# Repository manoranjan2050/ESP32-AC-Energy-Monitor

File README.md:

# ESP32-S3 AC Energy Monitor (6 CT + voltage), ESPHome / Home Assistant

An open-source, DIY mains energy monitor built on an **ESP32-S3 DevKit**:
- up to **6 SCT-013 current transformers (CTs)**, each channel works with **100A/50mA** or **30A/1V** CTs
- one **ZMPT101B** voltage sensor
- **ESPHome** firmware, visible in **Home Assistant**

> **⚠ Not a certified energy meter.** The ESP32 ADC is noisy and non-linear. Don't use this for
> billing or protection. The board has a **230 V section**, so build and test it only if you're
> competent with mains wiring.

---

## Project status (2026-09-24)

| Part | Status |
|---|---|
| Stage-1 test firmware (1 CT, true RMS, calibration in HA) | ✅ Working (`esphome/energy_monitor_test.yaml`) |
| CT input circuit (bias + 1k/1.8k + 104 + burden) | ✅ **Proven on a breadboard** with both CT types (results below) |
| Custom PCB v0.1 (KiCad): 6 CT + on-board ZMPT101B | ✅ Designed and **fully routed**. ERC 0, DRC 0 errors, schematic ↔ PCB parity 0. **Not built yet** |
| On-board ZMPT101B + MCP6002 voltage stage | ⚠ Designed, **not tested yet** |
| 6-channel + voltage firmware (real power, PF, kWh) | ⏳ Next step (after the PCB) |

### Breadboard test results (CT channel = same values as the PCB)

| CT | Load | Reading | Notes |
|---|---|---|---|
| 30A/1V | CT unclamped | ~0.08 A | Noise floor |
| 30A/1V | Light + fan | **0.33 A** | ≈ 75 W |
| 30A/1V | Water heater | **12.66 A** | Clean sine (pp/rms 2.86), no clipping |
| 100A/50mA + 24 Ω burden | Induction cooker | **4.6 A** | Stable, no clipping |

---

## Repository map

```
esphome/
  energy_monitor_test.yaml      Stage-1 test firmware (1 CT on GPIO1)
  secrets.example.yaml          Copy to secrets.yaml (git-ignored) and fill in Wi-Fi/keys
docs/wiring.md                  Stage-1 breadboard wiring checks
hardware/
  README.md                     PCB design notes, calculations, before-ordering checklist
  kicad/                        KiCad 10 project (schematic + routed PCB + ZMPT101B footprint + DRC rules)
  fab/                          Manufacturing files: Gerbers zip, BOM, pick-and-place, KiCad zip
  renders/                      Diagrams (SVG), PCB images, schematic PDF
  generate_kicad.py             Builds schematic + PCB from ONE netlist (source of truth)
  route_pcb.py                  Hand-routes mains, autoroutes the rest with Freerouting
  make_*_svg.py                 Regenerate the SVG diagrams from the same netlist
```

---

## Files you'll use

### KiCad (schematic + PCB)

| File | What it is |
|---|---|
| [`hardware/kicad/ct6-energy-monitor.kicad_pro`](hardware/kicad/ct6-energy-monitor.kicad_pro) | **Open this in KiCad 10** (free, kicad.org). The schematic and PCB open together |
| [`hardware/kicad/ct6-energy-monitor.kicad_sch`](hardware/kicad/ct6-energy-monitor.kicad_sch) | Schematic: 81 parts, 42 nets |
| [`hardware/kicad/ct6-energy-monitor.kicad_pcb`](hardware/kicad/ct6-energy-monitor.kicad_pcb) | Routed 2-layer PCB, 120 × 90 mm |
| [`hardware/fab/ct6-kicad-project.zip`](hardware/fab/ct6-kicad-project.zip) | The whole KiCad project in one zip |
| [`hardware/renders/schematic.pdf`](hardware/renders/schematic.pdf) | Schematic as a PDF, for viewing and printing |

### EasyEDA

- **EasyEDA Pro:** *File → Import → KiCad*, then pick `ct6-energy-monitor.kicad_pro` or `ct6-kicad-project.zip`.
  The files are **KiCad 10 format**, and EasyEDA's importer may only accept older KiCad versions (**not tested**).
- **EasyEDA Standard:** only imports old KiCad 5 files, so it won't work.
- **If the import fails**, you have three options:
  1. **Order straight from the Gerbers** (below). The board is already routed, so no EasyEDA is needed.
  2. **Redraw in EasyEDA** using [`easyeda_connection_guide.svg`](hardware/renders/easyeda_connection_guide.svg).
     It shows every part, every pin and its net name. Place the parts, put a **Net Label** with the exact
     name on each pin, then check the nets against the list in section 7 of that SVG.
  3. Ask for a **KiCad 6-format copy** of the schematic, which EasyEDA Pro is more likely to accept.

### v0.2 for EasyEDA: ESP32-S3-WROOM-1U module on board (in progress)

[`hardware/renders/easyeda_v02_wroom1u_guide.svg`](hardware/renders/easyeda_v02_wroom1u_guide.svg) is the
EasyEDA build guide for **v0.2**: 97 parts and 51 nets, every pin with its net name. It's generated by
`hardware/make_easyeda_v02_svg.py`.

**Changes from v0.1:**
- The DevKit sockets are replaced by **ESP32-S3-WROOM-1U-N16R8** (LCSC C3013946). Its U.FL connector takes an external IPEX antenna, which works much better from inside a metal DB box.
- **New support parts:**
  - **AMS1117-3.3** regulator
  - **USB-C with data** (D+ → IO20, D− → IO19) and **USBLC6-2SC6** ESD protection
  - **RESET/BOOT** buttons and a UART header
- **ZMPT101B backup:** **J8** takes the plug-in module, and jumper **JP2** selects what feeds GPIO9 (1-2 = on-board stage, 2-3 = module).
- **Unchanged:** the CT channels, bias, on-board voltage stage and GPIO map.

**v0.2 KiCad schematic** (schematic only; you lay out the v0.2 PCB in EasyEDA):
- [`hardware/kicad_v02/ct6-energy-monitor-v02.kicad_pro`](hardware/kicad_v02/ct6-energy-monitor-v02.kicad_pro): open in KiCad 10
- [`hardware/renders/schematic_v02.pdf`](hardware/renders/schematic_v02.pdf): PDF view
- [`hardware/fab/ct6-v02-kicad-schematic.zip`](hardware/fab/ct6-v02-kicad-schematic.zip): zipped project; try *EasyEDA Pro → File → Import → KiCad*
- [`hardware/kicad_v02/ct6-v02-bom.csv`](hardware/kicad_v02/ct6-v02-bom.csv): BOM

**Checks passed:**
- KiCad ERC: **0 electrical errors**
- **All 242 pin connections / 51 nets match** `hardware/netlist_v02.py`, which also generates the EasyEDA guide, so both always agree
- The module pinout was checked against KiCad's official ESP32-S3-WROOM-1 symbol

Regenerate with `python hardware/generate_kicad_v02.py`.

### Ordering (JLCPCB)

| File | Use |
|---|---|
| [`hardware/fab/ct6-gerbers-jlcpcb.zip`](hardware/fab/ct6-gerbers-jlcpcb.zip) | Upload as-is: Gerbers + drill, 2 layers |
| [`hardware/fab/ct6-bom.csv`](hardware/fab/ct6-bom.csv) | Bill of materials |
| [`hardware/fab/ct6-cpl.csv`](hardware/fab/ct6-cpl.csv) | Pick-and-place, origin = bottom-left board corner |

### Diagrams (SVG, open in any browser)

| Diagram | Shows |
|---|---|
| [`pcb_full_connection.svg`](hardware/renders/pcb_full_connection.svg) | **The complete PCB circuit**: every R, C, diode, jumper, op-amp pin and GPIO |
| [`easyeda_connection_guide.svg`](hardware/renders/easyeda_connection_guide.svg) | Every part as a card: pin → net name. Use it for EasyEDA redraws and checks |
| [`final_6ct_voltage_connection.svg`](hardware/renders/final_6ct_voltage_connection.svg) | Breadboard version: 6 CT + ready-made ZMPT101B module |
| [`breadboard_connection.svg`](hardware/renders/breadboard_connection.svg) | Breadboard test of one CT channel (the proven circuit) |
| [`pcb_top.png`](hardware/renders/pcb_top.png), [`pcb_copper.png`](hardware/renders/pcb_copper.png) | PCB 3D render and copper view |

---

## How the circuit works

### GPIO map (ESP32-S3, ADC1 only)

| Signal | GPIO | DevKit socket pin |
|---|---|---|
| CT1 | GPIO1 | J4-4 |
| CT2 · CT3 · CT4 · CT5 | GPIO4 · 5 · 6 · 7 | J3-4 · 5 · 6 · 7 |
| CT6 | GPIO8 | J3-12 |
| Voltage (ZMPT101B) | GPIO9 | J3-15 |
| Bias monitor | GPIO10 | J3-16 |
| I²C OLED SDA / SCL | GPIO17 / GPIO18 | J3-10 / J3-11 |
| 5V in / 3V3 / GND | — | J3-21 / J3-1,2 / J3-22, J4-1,21,22 |

Avoid GPIO0/3/45/46 (strapping), GPIO35–37 (octal PSRAM on N16R8) and GPIO11–20 (ADC2, conflicts with Wi-Fi).
**Measure your DevKit before ordering.** On the test board the silkscreen "4" was really GPIO1.

### One CT channel (×6, identical)

```
CT sleeve ─────────────────────────────────────── VB (bias ≈ 1.5 V)
CT tip ──┬── 1 kΩ ──┬── ADC node ──► GPIO
         │          ├── 1.8 kΩ ──► VB
       22 Ω         ├── 100 nF (104) ──► GND
     (burden,       └── BAT54S clamp (to GND and +3V3A)
   via jumper JP)
```

- **1 kΩ + 1.8 kΩ** scale the signal to **×0.643** around the bias. This gives headroom for 100 A, and the 1 kΩ limits current into the pin.
- **100 nF** filters noise (~2.5 kHz).
- **BAT54S** clamps the pin between 0 and 3.3 V. See "Diodes" below.

### Jumpers JP11…JP16 (one per CT)

| CT type | Shunt position | Burden | Home Assistant settings |
|---|---|---|---|
| **100A/50mA** (SCT-013-000) | **1-2 (mA), default** | IN | Burden **22** (or 24) · Secondary **0.05** · Primary **100** · Calibration **1.555** |
| **30A/1V** (SCT-013-030) | **2-3 (V)** | OUT | Burden **1** · Secondary **1** · Primary **30** · Calibration **1.555** |

- **1.555** undoes the ×0.643 divider. Fine-tune each channel: `Cal = 1.555 × (clamp-meter A ÷ reading A)`.
- **A 1V CT with the shunt on mA** reads ~25 % of the true value. That's safe, just obviously wrong.
- **⚠ A 100A CT with the shunt on V runs OPEN.** The reading clips to 0/4095 and can damage the CT or the pin. **Unclamp immediately.**
- Ship boards with every shunt on **1-2**.

### Diodes (D…)

| Designator | Part | Job |
|---|---|---|
| **D1** | SS34 Schottky | Power input: reverse-polarity protection, and stops USB 5V back-feeding your 5V supply |
| **D11 … D16** | BAT54S | ADC clamps for **CT1 … CT6** (D1**n** = CT**n**, so **D16 = CT6 → GPIO8**) |
| **D41** | BAT54S | ADC clamp for the voltage channel (GPIO9) |

A **BAT54S** is two Schottky diodes in series in one SOT-23:
- **pin 1 = GND side**
- **pin 2 = +3V3A side**
- **pin 3 = ADC node**

It does nothing while the signal is between 0 and 3.3 V. If a fault pushes the pin outside that range (for example a CT without its burden), it clamps the pin. The 1 kΩ in front limits the current. The clamps were optional on the breadboard; **fit them on the PCB.**

### Parts naming (per CT channel n = 1…6)

`J1n` jack · `R1n1` 22 Ω burden · `JP1n` mA/V jumper · `R1n2` 1 kΩ · `R1n3` 1.8 kΩ · `C1n` 100 nF · `D1n` BAT54S

### Resistor colour codes (4-band)

| Value | Bands |
|---|---|
| 10 kΩ | brown · black · orange |
| 1 kΩ | brown · black · red |
| 1.8 kΩ | brown · grey · red |
| 22 Ω | red · red · black |
| 24 Ω | red · yellow · black |
| 18 Ω | brown · grey · black (⚠ not 18 kΩ = brown · grey · orange) |

A ceramic cap marked **104** = 100 nF; **103** = 10 nF; **473** = 47 nF.

---

## Working on another PC

```bash
git clone https://github.com/manoranjan2050/ESP32-AC-Energy-Monitor.git
```

- **PCB:** install KiCad 10 and open `hardware/kicad/ct6-energy-monitor.kicad_pro`.
- **Firmware:** copy `esphome/secrets.example.yaml` to `esphome/secrets.yaml` (git-ignored) and fill in your Wi-Fi and keys.
- **Regenerate** (optional; this overwrites the KiCad files, so **don't** run it after editing the board by hand):

  ```bash
  "C:/Program Files/KiCad/10.0/bin/python.exe" hardware/generate_kicad.py
  ```

## Before ordering the PCB

1. Measure the **DevKit header row spacing** (22.86 mm) and check every pin used.
2. Check the **ZMPT101B pin grid**: 10.0 × 12.7 mm, with calipers.
3. **Screw terminals:** the wire entry faces the board edge.
4. Keep the **6.5 mm mains creepage** and the **slot under T1**.
5. **First power-up without mains and without CTs.** Expect +3V3A ≈ 3.3 V, VB ≈ 1.50 V, and every CTn_ADC / V_ADC ≈ 1.50 V.

Full details are in [`hardware/README.md`](hardware/README.md).

---

## Next steps

1. Order and build PCB v0.1, then test it: the CT channels first, then the on-board voltage stage (untested so far).
2. **6-channel + voltage ESPHome firmware:**
   - per-channel CT type, ratio and calibration
   - V + I sampled together for **real power, power factor, frequency and kWh**
   - Home Assistant **Energy dashboard** support

---

# Stage-1 test firmware guide (1 CT, breadboard)

> The sections below document the **first single-CT test**. Its bias circuit (10k/10k) and direct CT
> wiring were the starting point. The **final, proven channel circuit** adds the 1 kΩ / 1.8 kΩ / 104
> network shown above: use [`breadboard_connection.svg`](hardware/renders/breadboard_connection.svg) and set
> **Calibration 1.555**.

- Board: **ESP32-S3** (QFN56 rev v0.2, 16 MB flash, 8 MB PSRAM, native USB)
- ESPHome: **2026.8.2**, esp-idf framework
- Firmware: [`esphome/energy_monitor_test.yaml`](esphome/energy_monitor_test.yaml)
- Wiring checks: [`docs/wiring.md`](docs/wiring.md)

## 1. Hardware wiring (overview)

```
                     ESP32-S3 3V3
                          │
                         10k
                          │
             ┌────────────┼──────────── BIAS node (~1.65 V)
             │            │                 │
             │           10k            [10 µF, optional
             │            │              but recommended]
             │           GND                │
             │                             GND
   SCT-013-000
   ┌───────────┐
   │ lead A ───┼──────────┬──────── BIAS node
   │           │         22 Ω   (burden, directly across the CT leads)
   │ lead B ───┼──────────┴──────── ESP32-S3 GPIO1 (ADC1_CH0)
   └───────────┘
```

The CT drives an AC voltage across the 22 Ω burden. Because one end of the
burden sits on the 1.65 V bias node, the ADC pin sees **1.65 V ± the AC signal**.

## 2. ESP32 ADC pin configuration

Set the pin in the `substitutions:` block. Give the GPIO **number only**:

```yaml
ct_gpio: "1"     # GPIO1 = ADC1 channel 0 (check the pin electrically; header labels can be misleading)
```

On the ESP32-S3 use an **ADC1 pin, GPIO1 to GPIO10**. Skip GPIO3 (it's a strapping pin).
Don't use ADC2 (GPIO11 to GPIO20), because Wi-Fi uses ADC2.

- Attenuation is **12 dB**. On the S3 that gives about 0 to 3.1 V of usable range.
- Every sample is converted with ESP-IDF's **eFuse curve-fitting calibration**,
  so the ADC is not treated as linear. The diagnostic entity
  **CT ADC Calibration** shows which scheme is active. If it says
  `UNCALIBRATED`, the linear 3.3 V/4095 fallback is in use and the voltages are rough.

## 3. The 22 Ω burden resistor

The SCT-013-000 is a **current-output CT** (100 A : 50 mA) and has **no internal burden**.
The 22 Ω resistor turns its current into a voltage:

| Primary current | Secondary current | Burden RMS | Burden peak | ADC swing (around 1.65 V) |
|---|---|---|---|---|
| 1 A     | 0.5 mA  | 11 mV   | 15.6 mV | ±0.016 V |
| 4.35 A (1 kW) | 2.17 mA | 47.9 mV | 67.7 mV | ±0.068 V |
| 10 A    | 5 mA    | 110 mV  | 156 mV  | ±0.156 V |
| 50 A    | 25 mA   | 550 mV  | 778 mV  | ±0.78 V |
| ~90 A   | 45 mA   | 990 mV  | 1.40 V  | about the S3 ADC limit |
| 100 A   | 50 mA   | 1.10 V  | 1.556 V | **clips** (0.09 to 3.21 V) |

With 22 Ω the usable range is about 0 to 90 A. The **CT Clipped Samples** entity counts samples at the ADC rails.

## 4. The 2 × 10 k bias circuit

The two 10 k resistors from 3V3 to GND make a mid-rail point (~1.65 V), so the AC
signal swings around it instead of going below 0 V. Put a
**10 µF to 100 µF capacitor from the bias node to GND**. Without it the bias node
picks up ripple and noise, which shows up as a higher no-load RMS. The firmware
measures the real bias every window (**CT Bias Voltage**), so it doesn't need to be exactly 1.65 V.

## 5. SCT-013-000 connection

The 3.5 mm jack uses **tip** and **sleeve** for the two secondary leads. The ring is
normally unused. Polarity doesn't matter for RMS. Use a 3.5 mm breakout, or cut
the plug and solder the leads. **Fit the burden before clamping the CT on anything.**

## 6. Flashing the ESP32-S3

**Option A: ESPHome Builder (Home Assistant add-on)**
1. ESPHome Builder → **Secrets** (top-right). Add the lines from
   `esphome/secrets.yaml` (not in git; copy `esphome/secrets.example.yaml` and fill in your values) (`wifi_ssid`, `wifi_password`, `ct_test_api_key`,
   `ct_test_ota_password`, `ct_test_ap_password`).
2. **+ New device** → *Continue* → *Skip* the wizard, or create any device and then
   **Edit** it. Replace the whole YAML with `energy_monitor_test.yaml` and save.
3. **Install** → *Plug into this computer* (Chrome/Edge Web Serial), or
   *Manual download* → *Factory format* and flash with web.esphome.io.
4. Later updates can go over the air: **Install → Wirelessly**.

**Option B: ESPHome CLI on this PC**
```bash
cd "D:/My Project/ElectroIoT/ESP32-AC-Energy-Monitor/esphome"
```
```bash
python -m esphome run energy_monitor_test.yaml --device COM5
```
If the S3 won't enter download mode, hold **BOOT**, tap **RST**, then release BOOT.

## 7. Adding it to Home Assistant

The device uses the ESPHome native API, so HA should discover it automatically
(**Settings → Devices & services → Discovered: CT Energy Test → Configure**). When
asked for the encryption key, enter the `ct_test_api_key` value. If it isn't
discovered, add the **ESPHome** integration manually with host `ct-energy-test.local`
(or its IP address) and port `6053`.

Entities (all published together every **5 s**, one window each):

| Entity | Meaning |
|---|---|
| CT Raw ADC | Last raw 12-bit sample in the window |
| CT ADC Voltage | Last sample converted to volts (calibrated) |
| CT Bias Voltage | Mean of the window, which is the DC bias the RMS is taken around |
| CT Minimum / CT Maximum | Lowest and highest raw counts in the window |
| CT Peak-to-Peak | Calibrated V(max) − V(min) |
| CT AC RMS | **True RMS of the AC part across the burden** (bias removed; 400 samples over 10 cycles) |
| CT Secondary / Primary Current (estimated) | Only while **CT Current Estimate Enabled** is on |
| CT Burden Resistance, CT Rated Primary/Secondary Current, CT Calibration Factor | Editable config numbers, kept across reboots |
| CT Clipped Samples, CT Actual Sample Rate, CT ADC Calibration | Diagnostics |

The current estimate is:
```
secondary_A = CT_AC_RMS / burden_resistance
primary_A   = secondary_A × (ct_primary_current / ct_secondary_current) × calibration_factor
```

## 8. Expected values with NO load (CT unclamped or on a dead cable)

| Entity | Expected |
|---|---|
| CT Bias Voltage | ~1.60 to 1.70 V (depends on the 3V3 rail and resistor tolerance) |
| CT Raw ADC / Min / Max | Around the bias count, roughly 1900 to 2300, with Min and Max only a few dozen counts apart |
| CT Peak-to-Peak | Small, about 10 to 60 mV (ADC noise) |
| CT AC RMS | **Low, about 1 to 10 mV** (noise floor) |
| CT Clipped Samples | 0 |
| CT Actual Sample Rate | ~2000 Hz |

Note your no-load RMS. It is the noise floor. As a rough guide, 5 mV of noise
equals about 0.45 A of "phantom" primary current.

## 9. What changes when you clamp a live conductor

Clamp **one** insulated conductor (live **or** neutral), not the whole cable. If
you clamp live and neutral together, their currents cancel and you read about 0.

With a **1000 W resistive load** (~4.35 A at 230 V):

| Entity | Load off | Load on (theory) |
|---|---|---|
| CT Bias Voltage | ~1.65 V | **Unchanged** (~1.65 V) |
| CT Min / Max | ±a few counts | Spread out by roughly ±85 counts |
| CT Peak-to-Peak | ~0.03 V | **~0.14 V** |
| CT AC RMS | ~0.005 V | **~0.048 V** |
| Primary Current (est., if enabled) | ~0.2 to 0.5 A (noise) | **~4.3 A** |

The HA history graph for **CT AC RMS** should step up when the load turns on and
drop when it turns off. To calibrate, compare against a trusted clamp meter and set
`CT Calibration Factor = meter_amps / estimated_amps`. Tip: pass the conductor
through the CT **5 times** (5 turns), so 4.35 A reads like 21.7 A. That gives a much
better signal-to-noise ratio for calibration (divide by 5 afterwards).

## 10. Safety warnings

- **Mains voltage (230 V AC) can kill.** Only clamp an insulated conductor.
  Never open or modify live wiring on a breadboard setup. If you're unsure, have a
  licensed electrician install the CT.
- **Never leave the SCT-013-000 secondary open-circuit while it's clamped on a
  loaded conductor.** A current-output CT with no burden can produce dangerously
  high voltages and damage itself. Keep the 22 Ω burden fitted whenever the CT is
  plugged in or clamped.
- **Never connect the CT directly to the ESP32 without the burden and bias.** The
  ADC pin must stay between 0 V and 3.3 V. A loose bias wire leaves the pin
  swinging below 0 V, which can damage the GPIO.
- The burden must match the current range. 22 Ω clips above ~90 A. For higher
  currents use a smaller burden (for example 18 Ω).
- The ESP32 is powered from USB and is **not isolated from anything except through
  the CT's own insulation**. Keep the breadboard away from the mains side.
- This firmware is not a certified meter. Don't use it for billing, protection, or
  safety decisions.

---

## Original roadmap (written before the 1-channel test)

The 1-channel test has since passed, and the 6-CT PCB is designed. See **Project status** and **Next steps** at the top of this README.

```
ESP32-S3
├── CT1 … CT8   (ADC1 GPIO1..10; per-channel burden + calibration)
└── ZMPT101B    (voltage)
```
Planned: RMS voltage, RMS current per CT, real/apparent power, power factor,
frequency, kWh with the HA Energy dashboard, per-channel calibration, MQTT option, and OTA.
Eight CTs plus a ZMPT101B is 9 analog inputs, which fits in ADC1's 10 pins on the S3. Real power needs
V and I sampled nearly at the same time, so the stage-2 design will use interleaved sampling (or an external
ADC such as the ADS1115/ADS131M08).

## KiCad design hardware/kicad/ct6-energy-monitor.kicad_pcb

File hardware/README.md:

# CT6 Energy Monitor PCB (v0.1): ESP32-S3 DevKit + 6 CT + ZMPT101B

KiCad 10 project: [`kicad/ct6-energy-monitor.kicad_pro`](kicad/ct6-energy-monitor.kicad_pro)
**Full circuit diagram (every R/C/jumper/GPIO): [`renders/pcb_full_connection.svg`](renders/pcb_full_connection.svg)** · Schematic PDF: [`renders/schematic.pdf`](renders/schematic.pdf) · 3D top view: [`renders/pcb_top.png`](renders/pcb_top.png) · BOM: [`bom.csv`](bom.csv)

> **Status: v0.1 fully routed. Not yet built or tested; do the breadboard test and the checklist below first.**
> ERC: 0 violations · DRC: 0 errors, **0 unconnected**, 0 creepage/clearance · schematic-to-PCB parity: 0 issues.
> Remaining DRC warnings are cosmetic only (silkscreen text overlaps, and the jack's edge marker moved off Edge.Cuts).

**Manufacturing files** (`fab/`):
- `ct6-gerbers-jlcpcb.zip`: Gerbers + drill, upload to JLCPCB as-is
- `ct6-bom.csv` and `ct6-cpl.csv`: BOM and pick-and-place (origin = bottom-left board corner)
- `ct6-kicad-project.zip`: the whole KiCad project

**EasyEDA:** EasyEDA Pro → *File → Import → KiCad*, then select `ct6-kicad-project.zip` (or the `.kicad_pro`).
The files are KiCad 10 format; if your EasyEDA version refuses them, order from the Gerber zip instead.
EasyEDA Standard only imports old KiCad 5 files.

Everything is generated from one netlist in [`generate_kicad.py`](generate_kicad.py), and routed by [`route_pcb.py`](route_pcb.py):
1. The 230 V nets are hand-routed as locked 0.8 mm tracks.
2. **Freerouting 1.9.0** autoroutes the rest, with the whole mains block (+6.5 mm) set as a keepout.
3. The GND pour is added last.

```bash
set CT6_NO_ZONES=1
"C:/Program Files/KiCad/10.0/bin/python.exe" hardware/generate_kicad.py
"C:/Program Files/KiCad/10.0/bin/python.exe" hardware/route_pcb.py path/to/freerouting-1.9.0.jar
```

⚠ Both scripts overwrite the `.kicad_pcb`. **If you edit the board by hand in KiCad, stop rerunning them.**

---

## Block diagram

```
 5V terminal / USB-C ─ polyfuse ─ SS34 ─► DevKit 5V ──► DevKit 3V3 ─ ferrite ─► +3V3A (analog)
                                                                               │
 +3V3A ─ 12k/10k ─► MCP6002-A buffer ─ 47R ─► VB = 1.50 V (10µF+100nF) ────────┼──► GPIO10 (bias monitor)
                                                                               │
 CT1..CT6 jack ─► [22R burden via mA/V jumper] ─ 1k ─┬─ 1k8 → VB              │
                                                      ├─ 100nF → GND           │
                                                      └─ BAT54S clamp ─► GPIO1,4,5,6,7,8
                                                                               │
 230V L/N ─ fuse 100mA ─ MOV ─ 4×220k ─► ZMPT101B ─► MCP6002-B TIA (2k7‖47nF) ─ 1k ─ BAT54S ─► GPIO9
```

## CT input channel (copied from KinCony KC868-M16v2, per channel)

| Part | Value | Purpose |
|---|---|---|
| J1n | 3.5 mm jack (SJ1-3523N) | **Tip = signal, Sleeve = VB**, Ring unused (SCT-013 wiring) |
| R1n1 | **22 Ω 0.1 %** | Burden for **mA-type** CTs (SCT-013-000 100 A/50 mA) |
| JP1n | 3-pin header | **1-2 = mA** (burden in, **ship with this fitted**); **2-3 = V** (burden out, for 1 V CTs such as SCT-013-030) |
| R1n2 / R1n3 | 1 kΩ / 1.8 kΩ 1 % | Attenuator: ×0.643 around VB. The 1 k limits current into the pin; the 1k8 holds an empty jack at VB |
| C1n | 100 nF | Anti-alias / noise filter, ~2.5 kHz |
| D1n | BAT54S | Clamps the ADC pin between GND and 3V3A |

**Headroom at the ADC pin** (1.50 V bias; S3 12 dB range is about 0 to 3.1 V):

| CT | At full scale | At the pin |
|---|---|---|
| SCT-013-000 + 22 Ω (jumper **mA**) | 100 A → 1.10 V RMS | ±1.00 V peak → 0.50 to 2.50 V ✅ |
| SCT-013-030 1 V (jumper **V**) | 30 A → 1.00 V RMS | ±0.91 V peak → 0.59 to 2.41 V ✅ |

Firmware scale (amps per RMS volt **measured at the pin**) = CT ratio ÷ 0.643:
- 100 A/50 mA + 22 Ω: 100 / 0.05 / 22 / 0.643 = **141.4 A/V**
- 30 A/1 V: 30 / 0.643 = **46.7 A/V**

Then fine-tune each channel's calibration factor against a clamp meter.

A **wrong jumper in one direction is safe**: a 1 V CT with the jumper on mA reads only **~25 % of the true value**, because its internal ~67 Ω burden ends up in parallel with the 22 Ω. It's obviously wrong, but harmless. **The dangerous case is an mA CT with the jumper on V.** In that state the CT runs open (the 0/4095 clipping from the breadboard test). That is why mA is the default and the 1k series resistor plus BAT54S protect the pin.

## Voltage channel (ZMPT101B, on board)

- **Primary:** 230 V → F2 100 mA T → 4 × 220 kΩ 1206 (880 kΩ, 57 V per resistor) → 0.26 mA. RV1 (275 VAC MOV) across L/N after the fuse.
- **Secondary:** into MCP6002-B used as a **transimpedance amplifier** with its + input at VB. Output = VB − 0.26 mA × 2.7 kΩ = **1.50 V ± 0.70 V RMS** (±1.0 V peak at 230 V, ±1.2 V at 270 V). 47 nF in parallel sets a ~1.25 kHz roll-off.
- Output goes through 1 kΩ + 100 nF + BAT54S to GPIO9. Calibrate volts in firmware; there's no trimmer.

## GPIO map (ESP32-S3, all ADC1)

| Signal | GPIO | DevKitC-1 pin |
|---|---|---|
| CT1 | GPIO1 | J3-4 (right header) |
| CT2 to CT6 | GPIO4, 5, 6, 7, 8 | J1-4..7, J1-12 (left header) |
| Voltage | GPIO9 | J1-15 |
| Bias monitor | GPIO10 | J1-16 |
| I2C OLED SDA / SCL | GPIO17 / GPIO18 | J1-10 / J1-11 |

Not used: GPIO0/3/45/46 (strapping), GPIO35 to 37 (octal PSRAM on N16R8), GPIO11 to 20 (ADC2, conflicts with Wi-Fi).

## PCB (120 × 90 mm, 2-layer)

- **Mains block** (top-left) is fenced by an **L-shaped 1.6 mm routed slot**. The slot's vertical leg runs **under the ZMPT101B** between primary and secondary pins (10 mm pin-to-pin).
- **Custom DRC rules** (`kicad/ct6-energy-monitor.kicad_dru`): **6.5 mm clearance and creepage** from any `AC_*` net to all low-voltage copper.
- **GND pour** on both layers covers the LV area only. It excludes the mains block and the **DevKit antenna area** (top-right; the DevKit's antenna end sits at the top board edge).
- CT jacks sit on the bottom edge. The DevKit's USB end points down into a clear area, so you can still plug in a USB cable for flashing.

## Before ordering (checklist)

1. **Measure your DevKit.** Header row spacing is set to **22.86 mm** (`DEVKIT_ROW_SPACING`), and the pin order is ESP32-S3-DevKitC-1. Your breadboard test showed the silkscreen didn't match the actual pin (the wire on "4" was GPIO1). **Check every pin used here with a meter or the pin-scan firmware.**
2. **ZMPT101B footprint:** 10.0 × 12.7 mm pin grid, cross-checked against two independent KiCad libraries. Check it against your part with calipers.
3. **Screw terminals J1/J5:** make sure the wire entry faces the board edge (rotate 180° in KiCad if not).
4. **Review the autorouted tracks** in KiCad. Autorouters are functional, not beautiful. The CT signal traces to the DevKit are long diagonals, which is fine at 50 Hz, but you may want to tidy them.
5. After any change, run DRC. It must show **0 unconnected items and 0 creepage errors**.
6. Mains safety: 230 V on a PCB needs an enclosure, a fuse, and no exposed metal. The ZMPT101B is the isolation barrier, so don't bypass it.

## Firmware

Not written yet. Extending `esphome/energy_monitor_test.yaml` to 6 CT + V gives:
- per-channel `ct_gpio`, CT type (mA/V), ratio and calibration
- interleaved V + I sampling for real power, PF and kWh

The on-board **attenuator (×0.643) must be included** in the scale; see the formulas above.

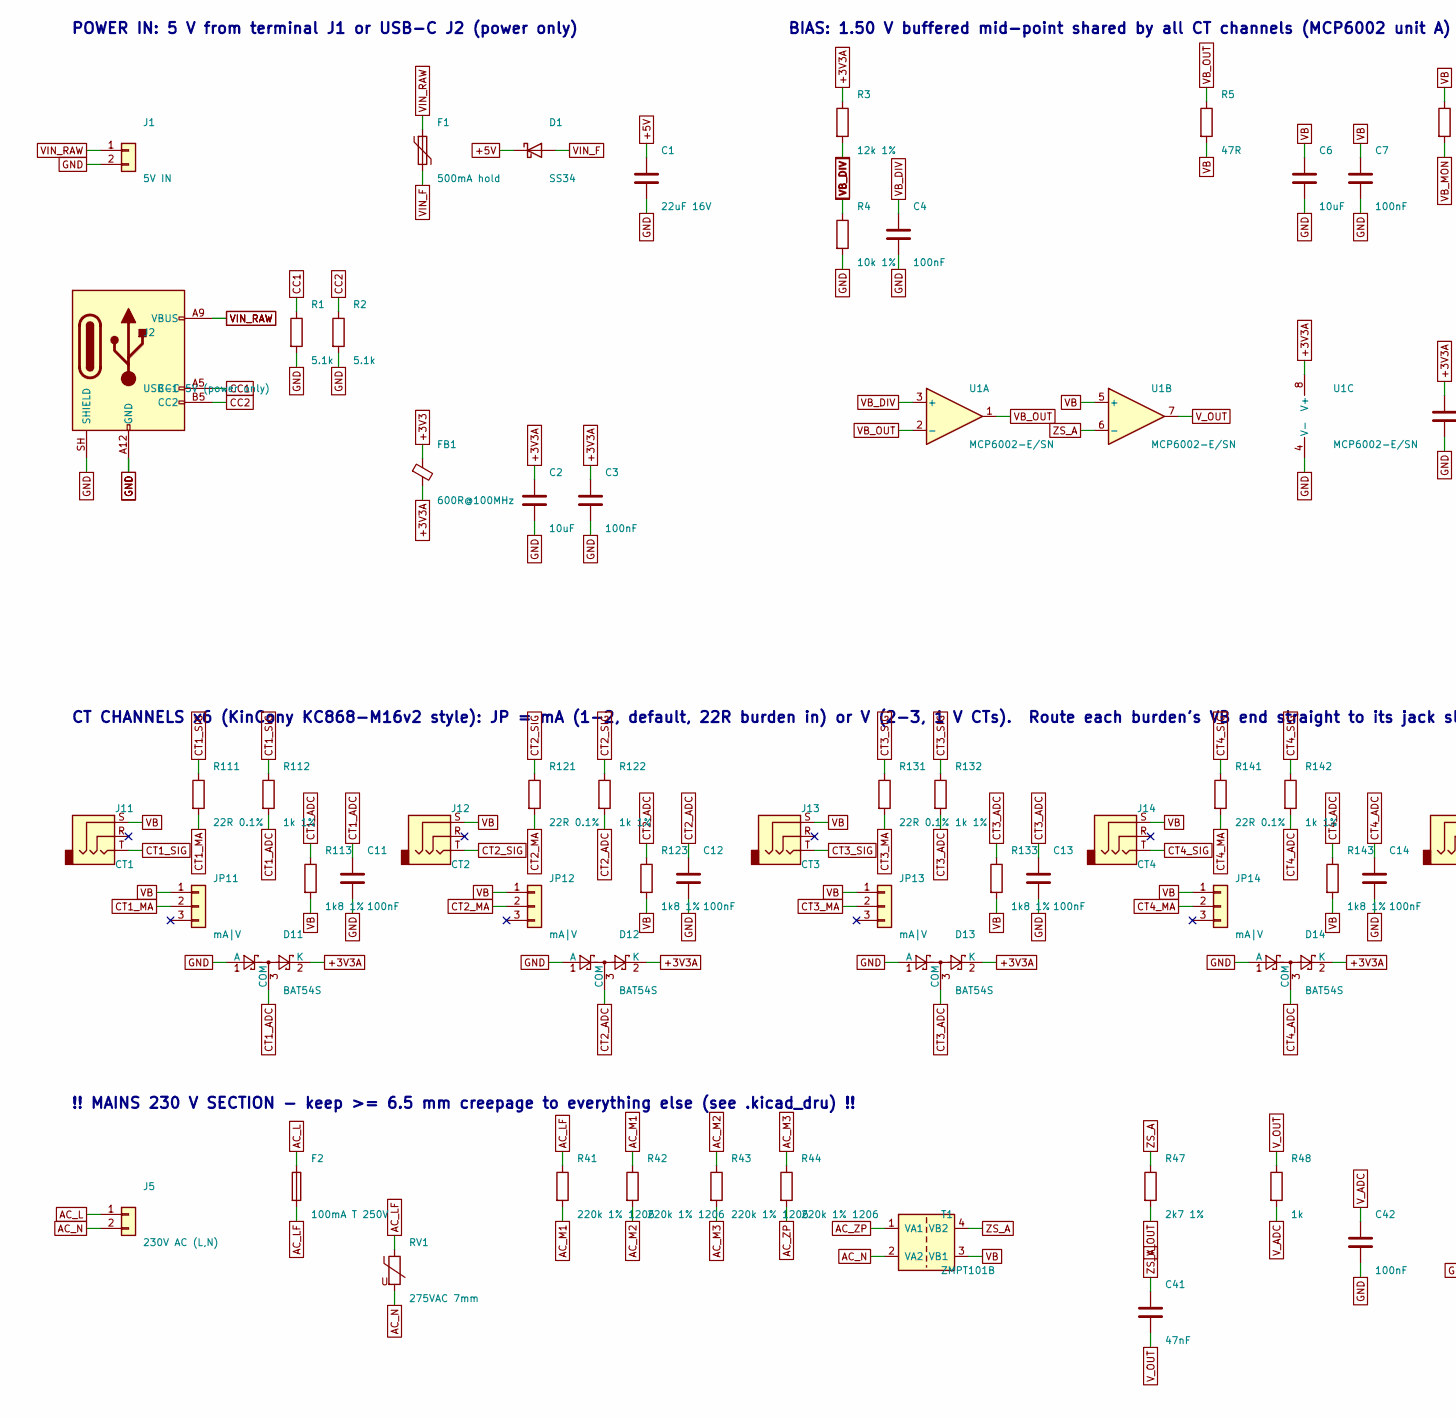
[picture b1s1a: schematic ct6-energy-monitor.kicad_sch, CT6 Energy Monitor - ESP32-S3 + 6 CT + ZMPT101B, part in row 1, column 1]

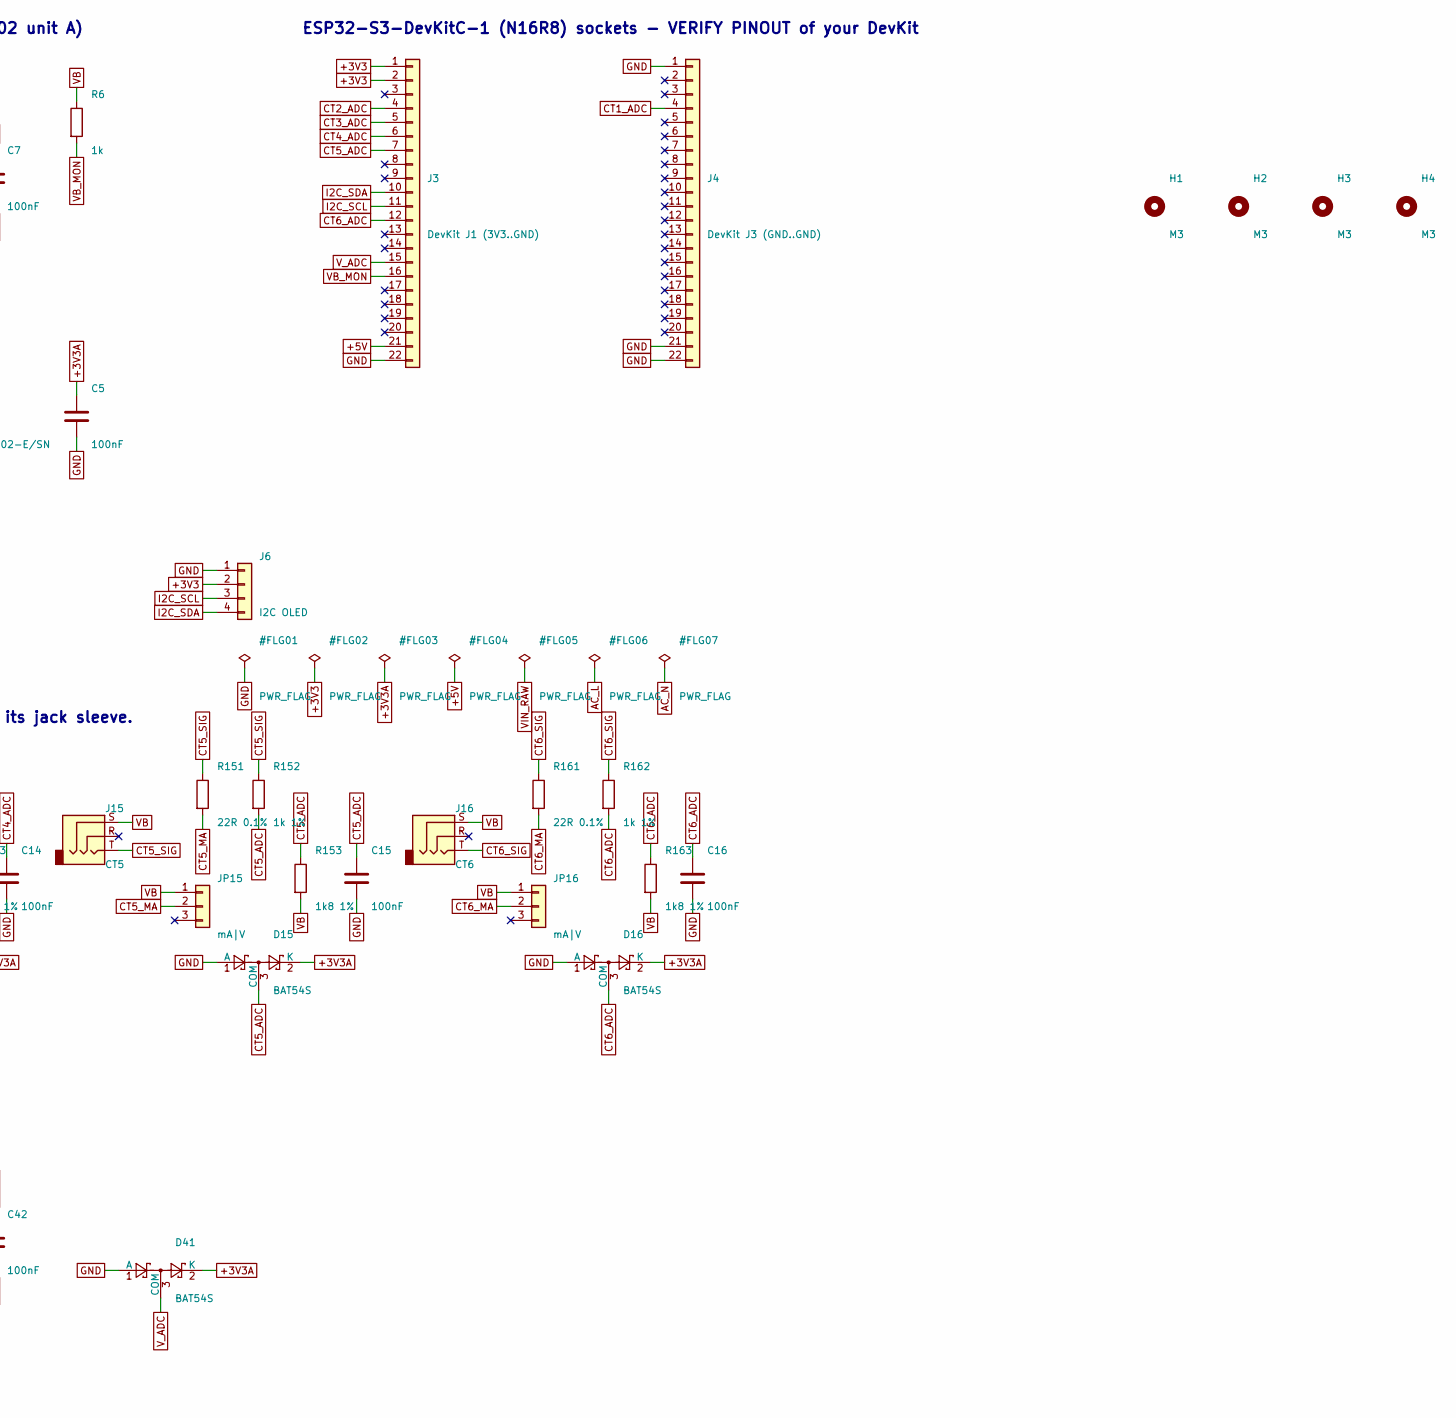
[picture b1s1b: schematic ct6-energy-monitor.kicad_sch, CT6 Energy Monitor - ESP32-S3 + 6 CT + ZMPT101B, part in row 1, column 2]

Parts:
C1: 22uF 16V; C_1206_3216Metric
C2, C6: 10uF; C_0805_2012Metric
C3, C4, C5, C7, C11, C12, C13, C14, C15, C16, C42: 100nF; C_0805_2012Metric
C41: 47nF; C_0805_2012Metric
D1: SS34; D_SMA
D11, D12, D13, D14, D15, D16, D41: BAT54S; SOT-23
F1: 500mA hold; Fuse_1206_3216Metric
F2: 100mA T 250V; Fuse_Littelfuse_395Series
FB1: 600R@100MHz; L_0805_2012Metric
H1, H2, H3, H4: M3; MountingHole_3.2mm_M3
J1: 5V IN; TerminalBlock_Phoenix_MKDS-1,5-2-5.08_1x02_P5.08mm_Horizont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
J2: USB-C 5V (power only); USB_C_Receptacle_GCT_USB4125-xx-x_6P_TopMnt_Horizontal
J3: DevKit J1 (3V3..GND); PinSocket_1x22_P2.54mm_Vertical
J4: DevKit J3 (GND..GND); PinSocket_1x22_P2.54mm_Vertical
J5: 230V AC (L,N); TerminalBlock_Phoenix_MKDS-1,5-2-5.08_1x02_P5.08mm_Horizont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
J6: I2C OLED; PinHeader_1x04_P2.54mm_Vertical
J11: CT1; Jack_3.5mm_CUI_SJ1-3523N_Horizontal
J12: CT2; Jack_3.5mm_CUI_SJ1-3523N_Horizontal
J13: CT3; Jack_3.5mm_CUI_SJ1-3523N_Horizontal
J14: CT4; Jack_3.5mm_CUI_SJ1-3523N_Horizontal
J15: CT5; Jack_3.5mm_CUI_SJ1-3523N_Horizontal
J16: CT6; Jack_3.5mm_CUI_SJ1-3523N_Horizontal
JP11, JP12, JP13, JP14, JP15, JP16: mA|V; PinHeader_1x03_P2.54mm_Vertical
R1, R2: 5.1k; R_0805_2012Metric
R3: 12k 1%; R_0805_2012Metric
R4: 10k 1%; R_0805_2012Metric
R5: 47R; R_0805_2012Metric
R6, R48: 1k; R_0805_2012Metric
R41, R42, R43, R44: 220k 1% 1206; R_1206_3216Metric
R47: 2k7 1%; R_0805_2012Metric
R111, R121, R131, R141, R151, R161: 22R 0.1%; R_0805_2012Metric
R112, R122, R132, R142, R152, R162: 1k 1%; R_0805_2012Metric
R113, R123, R133, R143, R153, R163: 1k8 1%; R_0805_2012Metric
RV1: 275VAC 7mm; RV_Disc_D7mm_W4.2mm_P5mm
T1: ZMPT101B
U1: MCP6002-E/SN; SOIC-8_3.9x4.9mm_P1.27mm

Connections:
+3V3: FB1.1, J3.1, J3.2, J6.2
+3V3A: C2.1, C3.1, C5.1, D11.2 (K), D12.2 (K), D13.2 (K), D14.2 (K), D15.2 (K), D16.2 (K), D41.2 (K), FB1.2, R3.1, U1.8 (V+)
+5V: C1.1, D1.1 (K), J3.21
AC_L: F2.1, J5.1
AC_LF: F2.2, R41.1, RV1.1
AC_M1: R41.2, R42.1
AC_M2: R42.2, R43.1
AC_M3: R43.2, R44.1
AC_N: J5.2, RV1.2, T1.2 (VA2)
AC_ZP: R44.2, T1.1 (VA1)
CC1: J2.A5 (CC1), R1.1
CC2: J2.B5 (CC2), R2.1
CT1_ADC: C11.1, D11.3 (COM), J4.4, R112.2, R113.1
CT1_MA: JP11.2, R111.2
CT1_SIG: J11.T, R111.1, R112.1
CT2_ADC: C12.1, D12.3 (COM), J3.4, R122.2, R123.1
CT2_MA: JP12.2, R121.2
CT2_SIG: J12.T, R121.1, R122.1
CT3_ADC: C13.1, D13.3 (COM), J3.5, R132.2, R133.1
CT3_MA: JP13.2, R131.2
CT3_SIG: J13.T, R131.1, R132.1
CT4_ADC: C14.1, D14.3 (COM), J3.6, R142.2, R143.1
CT4_MA: JP14.2, R141.2
CT4_SIG: J14.T, R141.1, R142.1
CT5_ADC: C15.1, D15.3 (COM), J3.7, R152.2, R153.1
CT5_MA: JP15.2, R151.2
CT5_SIG: J15.T, R151.1, R152.1
CT6_ADC: C16.1, D16.3 (COM), J3.12, R162.2, R163.1
CT6_MA: JP16.2, R161.2
CT6_SIG: J16.T, R161.1, R162.1
GND: C1.2, C2.2, C3.2, C4.2, C5.2, C6.2, C7.2, C11.2, C12.2, C13.2, C14.2, C15.2, C16.2, C42.2, D11.1 (A), D12.1 (A), D13.1 (A), D14.1 (A), D15.1 (A), D16.1 (A), D41.1 (A), J1.2, J2.A12 (GND), J2.B12 (GND), J2.SH (SHIELD), J3.22, J4.1, J4.21, J4.22, J6.1, R1.2, R2.2, R4.2, U1.4 (V-)
I2C_SCL: J3.11, J6.3
I2C_SDA: J3.10, J6.4
VB: C6.1, C7.1, J11.S, J12.S, J13.S, J14.S, J15.S, J16.S, JP11.1, JP12.1, JP13.1, JP14.1, JP15.1, JP16.1, R5.2, R6.1, R113.2, R123.2, R133.2, R143.2, R153.2, R163.2, T1.3 (VB1), U1.5 (+)
VB_DIV: C4.1, R3.2, R4.1, U1.3 (+)
VB_MON: J3.16, R6.2
VB_OUT: R5.1, U1.1, U1.2 (-)
VIN_F: D1.2 (A), F1.2
VIN_RAW: F1.1, J1.1, J2.A9 (VBUS), J2.B9 (VBUS)
V_ADC: C42.1, D41.3 (COM), J3.15, R48.2
V_OUT: C41.2, R47.2, R48.1, U1.7
ZS_A: C41.1, R47.1, T1.4 (VB2), U1.6 (-)

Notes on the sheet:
POWER IN: 5 V from terminal J1 or USB-C J2 (power only)
BIAS: 1.50 V buffered mid-point shared by all CT channels (MCP6002 unit A)
CT CHANNELS x6 (KinCony KC868-M16v2 style): JP = mA (1-2, default, 22R burden in) or V (2-3, 1 V CTs). Route each burden's VB end straight to its jack sleeve.
!! MAINS 230 V SECTION - keep >= 6.5 mm creepage to everything else (see .kicad_dru) !!
ESP32-S3-DevKitC-1 (N16R8) sockets - VERIFY PINOUT of your DevKit

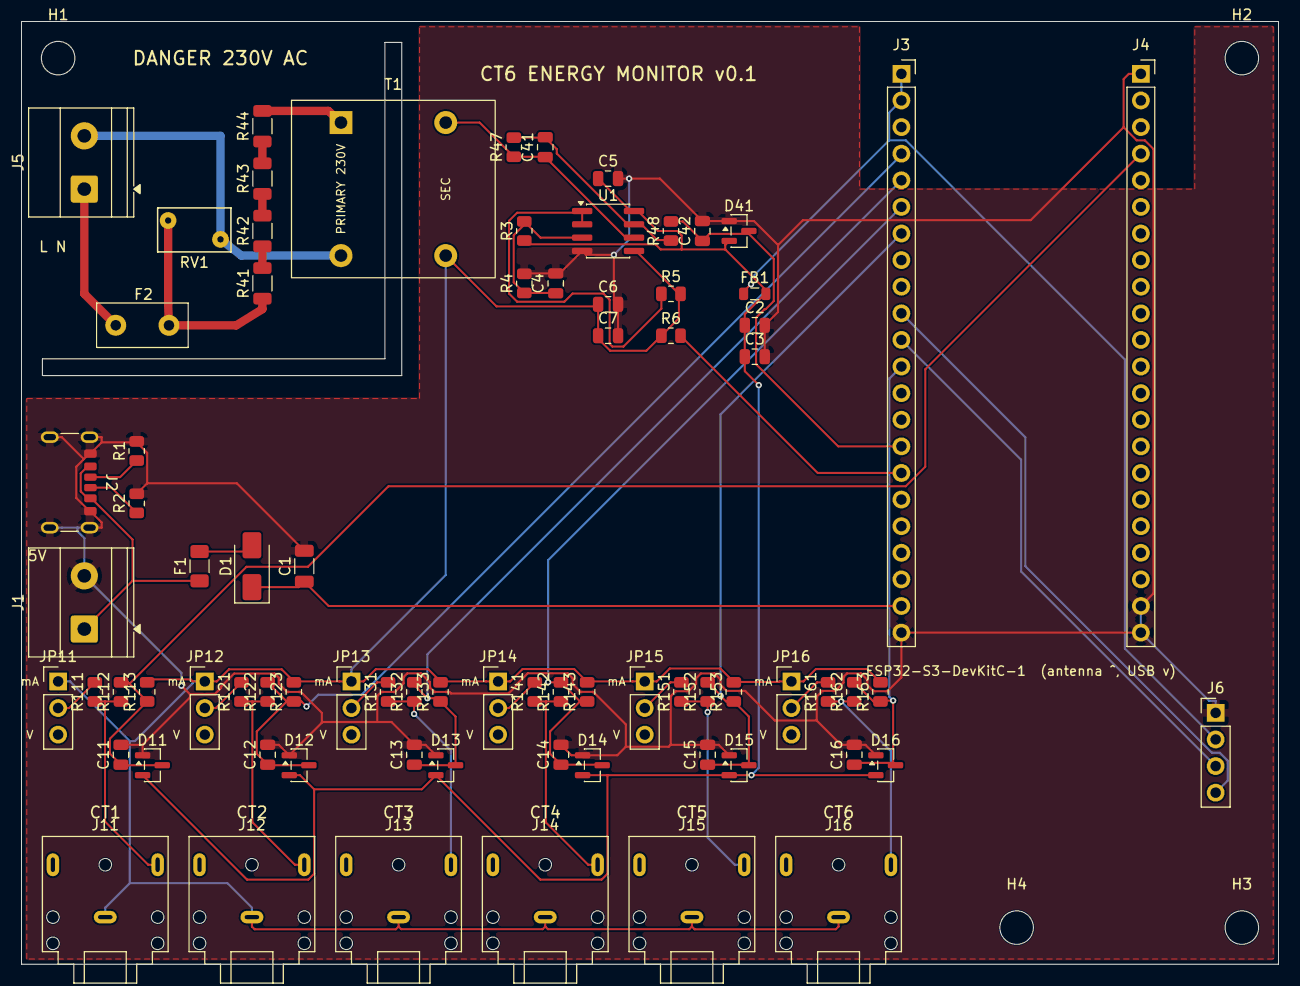
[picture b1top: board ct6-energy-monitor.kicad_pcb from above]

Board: 2 copper layers, 120.0 x 90.0 mm, 81 parts (0 on the bottom side), 42 nets.

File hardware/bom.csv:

"Reference","Value","Footprint","QUANTITY"
"C1","22uF 16V","Capacitor_SMD:C_1206_3216Metric","1"
"C2,C6","10uF","Capacitor_SMD:C_0805_2012Metric","2"
"C3-C5,C7,C11-C16,C42","100nF","Capacitor_SMD:C_0805_2012Metric","11"
"C41","47nF","Capacitor_SMD:C_0805_2012Metric","1"
"D1","SS34","Diode_SMD:D_SMA","1"
"D11-D16,D41","BAT54S","Package_TO_SOT_SMD:SOT-23","7"
"F1","500mA hold","Fuse:Fuse_1206_3216Metric","1"
"F2","100mA T 250V","Fuse:Fuse_Littelfuse_395Series","1"
"FB1","600R@100MHz","Inductor_SMD:L_0805_2012Metric","1"
"J1","5V IN","TerminalBlock_Phoenix:TerminalBlock_Phoenix_MKDS-1,5-2-5.08_1x02_P5.08mm_Horizontal","1"
"J2","USB-C 5V (power only)","Connector_USB:USB_C_Receptacle_GCT_USB4125-xx-x_6P_TopMnt_Horizontal","1"
"J3","DevKit J1 (3V3..GND)","Connector_PinSocket_2.54mm:PinSocket_1x22_P2.54mm_Vertical","1"
"J4","DevKit J3 (GND..GND)","Connector_PinSocket_2.54mm:PinSocket_1x22_P2.54mm_Vertical","1"
"J5","230V AC (L,N)","TerminalBlock_Phoenix:TerminalBlock_Phoenix_MKDS-1,5-2-5.08_1x02_P5.08mm_Horizontal","1"
"J6","I2C OLED","Connector_PinHeader_2.54mm:PinHeader_1x04_P2.54mm_Vertical","1"
"J11","CT1","Connector_Audio:Jack_3.5mm_CUI_SJ1-3523N_Horizontal","1"
"J12","CT2","Connector_Audio:Jack_3.5mm_CUI_SJ1-3523N_Horizontal","1"
"J13","CT3","Connector_Audio:Jack_3.5mm_CUI_SJ1-3523N_Horizontal","1"
"J14","CT4","Connector_Audio:Jack_3.5mm_CUI_SJ1-3523N_Horizontal","1"
"J15","CT5","Connector_Audio:Jack_3.5mm_CUI_SJ1-3523N_Horizontal","1"
"J16","CT6","Connector_Audio:Jack_3.5mm_CUI_SJ1-3523N_Horizontal","1"
"JP11-JP16","mA|V","Connector_PinHeader_2.54mm:PinHeader_1x03_P2.54mm_Vertical","6"
"R1,R2","5.1k","Resistor_SMD:R_0805_2012Metric","2"
"R3","12k 1%","Resistor_SMD:R_0805_2012Metric","1"
"R4","10k 1%","Resistor_SMD:R_0805_2012Metric","1"
"R5","47R","Resistor_SMD:R_0805_2012Metric","1"
"R6,R48","1k","Resistor_SMD:R_0805_2012Metric","2"
"R41-R44","220k 1% 1206","Resistor_SMD:R_1206_3216Metric","4"
"R47","2k7 1%","Resistor_SMD:R_0805_2012Metric","1"
"R111,R121,R131,R141,R151,R161","22R 0.1%","Resistor_SMD:R_0805_2012Metric","6"
"R112,R122,R132,R142,R152,R162","1k 1%","Resistor_SMD:R_0805_2012Metric","6"
"R113,R123,R133,R143,R153,R163","1k8 1%","Resistor_SMD:R_0805_2012Metric","6"
"RV1","275VAC 7mm","Varistor:RV_Disc_D7mm_W4.2mm_P5mm","1"
"T1","ZMPT101B","ct6:ZMPT101B","1"
"U1","MCP6002-E/SN","Package_SO:SOIC-8_3.9x4.9mm_P1.27mm","1"

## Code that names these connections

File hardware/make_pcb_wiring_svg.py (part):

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pill(1040, yA - 66, "+3V3A", RED, 52)
line(1065, yA + 20, 1065, yA + 45); diode_up(1065, yA + 45, yA + 75); gnd(1065, yA + 75)
text(1077, yA - 12, "D41", 10, TXT, "700"); text(1077, yA, "BAT54S", 9.5, SUB)
pill(1100, yA + 20, "→ GPIO9 (V_ADC)", PUR)
text(700, yM + 235, "T1 primary 0.26 mA at 230 V → U1B transimpedance (R47 2k7) → ≈0.70 V RMS around VB → R48/C42 filter → GPIO9",
     11.5, SUB, italic=True)

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text(1500, 144, "plugs into sockets J3 (left header) + J4 (right header)", 11.5, "#b9c7d4")
rows = [("J3-1, J3-2", "3V3", "+3V3 → FB1 / J6", RED), ("J3-21", "5V", "+5V ← D1", RED),
        ("J3-22, J4-1/21/22", "GND", "⏚ GND", "#aaaaaa"),
        ("J4-4", "GPIO1", "CT1_ADC", ORG), ("J3-4", "GPIO4", "CT2_ADC", ORG), ("J3-5", "GPIO5", "CT3_ADC", ORG),
        ("J3-6", "GPIO6", "CT4_ADC", ORG), ("J3-7", "GPIO7", "CT5_ADC", ORG), ("J3-12", "GPIO8", "CT6_ADC", ORG),
        ("J3-15", "GPIO9", "V_ADC (voltage)", PUR), ("J3-16", "GPIO10", "VB_MON (bias)", BLU),
        ("J3-10", "GPIO17", "I2C_SDA → J6-4", "#8ea1b5"), ("J3-11", "GPIO18", "I2C_SCL → J6-3", "#8ea1b5")]
text(1500, 178, "Socket pin", 11.5, "#b9c7d4", "700"); text(1630, 178, "GPIO", 11.5, "#b9c7d4", "700")
text(1710, 178, "Net / use", 11.5, "#b9c7d4", "700")
for k, (sp, gpio, net, c) in enumerate(rows):
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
